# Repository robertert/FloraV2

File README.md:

# Doniczka-robot

Autonomiczna, solarna, mobilna doniczka: jezdzi po trawniku za sloncem, mierzy
warunki i sama podlewa rosline. Praca inzynierska AGH, termin styczen 2027.

Cos nie dziala przy uruchamianiu? Zacznij od `CZESTE_BLEDY.md`.

## Uklad repozytorium

Jedno repo, dwie jednostki polaczone UART-em przez maszt, wspolne sterowniki.

```
components/        sterowniki dzielone przez obie jednostki
  flora_board/     mapa pinow bryly + przeliczniki odometrii
  flora_motors/    naped na Cytron MDD10A (PWM + DIR)
  flora_encoders/  enkodery kwadraturowe na PCNT
  flora_ina226/    pomiar pradu i napiecia szyny 12V
  flora_msgs/      kontrakt wiadomosci UART (wspolny dla obu stron)
hub/               BRYLA: ESP32-S3 DevKitC-1 N16R8
                   naped, odometria, zasilanie, podlewanie, telemetria
node/              GLOWICA MASZTU: ESP32-S3 z gniazdem kamery (do kupienia)
                   kompas sloneczny, BME280, IMU, czujnik deszczu
```

Nazwy katalogow `hub` i `node` pochodza z wczesniejszej wersji projektu.
`hub` to jednostka DOLNA, `node` to GLOWICA.

Wspolne komponenty trafiaja do obu projektow przez `EXTRA_COMPONENT_DIRS`
ustawione w `CMakeLists.txt` kazdej jednostki.

## Wymagania

ESP-IDF **v6.1**, zainstalowane przez EIM w `~/.espressif/v6.1/esp-idf`.
Obie jednostki to ESP32-S3.

## Praca z projektem

`./dev.sh` sam wciaga srodowisko ESP-IDF i wykrywa port, wiec nie trzeba
niczego sourcowac:

```sh
./dev.sh hub build      # zbuduj bryle
./dev.sh hub fm         # build + flash + monitor, najczestszy cykl
./dev.sh hub monitor    # sama konsola, wyjscie Ctrl+]
./dev.sh hub menuconfig
./dev.sh ports          # co widac na USB
./dev.sh help           # pelna lista komend
```

Nieznane komendy leca wprost do `idf.py`, np. `./dev.sh hub partition-table`.

Przy dwoch podlaczonych plytkach trzeba wskazac port:
`FLORA_PORT=/dev/cu.usbmodem101 ./dev.sh hub fm`.

## Debug przez MQTT

Bryla publikuje wszystko, co do niej dociera (wlasne czujniki i wiadomosci
glowicy), pod `flora/robot1/tele/*` i `flora/robot1/head/*`, a komendy
przyjmuje z `flora/robot1/cmd/*` (opis w `hub/main/hub_remote.h`).

1. Broker na Macu (`brew install mosquitto`):
   `mosquitto -c tools/dashboard/mosquitto.conf -v`
2. Adres brokera dla robota to IP Maca w tej samej sieci:
   `FLORA_MQTT_URI_DEFAULT` w `flora_board.h` albo klucz `mqtt_uri` w NVS.
3. Panel: otworz `tools/dashboard/index.html` w przegladarce, adres
   `ws://<ip-maca>:9001`. Strzalki na klawiaturze jada, spacja to STOP.
4. Z terminala: `mosquitto_sub -t 'flora/robot1/#' -v`,
   `mosquitto_pub -t flora/robot1/cmd/pump -m on`.

Naped z panelu staje sam po 1,5 s bez odswiezenia komendy (dead-man),
wiec zerwane WiFi nie zostawi jadacego robota.

**Do jakiego brokera laczy sie robot** - po kolei, az ktorys odpowie:

1. ustawienia z NVS (zmieniane zdalnie, patrz nizej),
2. serwer wkompilowany w firmware (`FLORA_MQTT_URI_DEFAULT` w `flora_board.h`,
   TLS, login `robot1`, haslo z NVS - w kodzie go nie ma),
3. broker na Macu po nazwie mDNS (`Roberts-MacBook-Pro.local`), bez hasel.

Haslo brokera trzeba wpisac raz (`cmd/config/mqtt_pass`, z lokalnego panelu,
gdy robot jest na brokerze Maca). Przezywa zwykle flashowanie, znika dopiero
po `erase-flash`.

**Ustawienia zdalnie** (karta "Ustawienia" w panelu albo z terminala), zapis
do NVS, siec i broker dzialaja po restarcie:

```sh
mosquitto_pub -t flora/robot1/cmd/config/mqtt_uri -m mqtt://172.20.10.14:1883
mosquitto_pub -t flora/robot1/cmd/reboot -m 1
```

Klucze: `wifi_ssid`, `wifi_pass`, `mqtt_uri`, `mqtt_user`, `mqtt_pass`,
`soil_dry`, `soil_wet`; wartosc `-` kasuje ustawienie. Zly adres albo haslo
w NVS nie wymaga podlaczania kabla - robot przejdzie do kolejnych prob.

**Diagnostyka zdalna** (`hub/main/hub_diag.c`):

- `tele/log` - ostrzezenia i bledy z logu ESP (poziomy W i E). Kolejka
  trzyma je takze bez polaczenia, wiec bledy z uruchamiania i z przerwy w
  sieci wychodza po polaczeniu. Konsola USB dostaje wszystko jak dotad.
- `tele/boot` (retain) - wersja firmware, data budowania, powod ostatniego
  restartu (`panic`, `task_wdt`, `brownout`... = awaria) i licznik startow.

Wersja firmware pochodzi z tagu `hub-vX.Y.Z` (`git tag hub-v0.1.0`); bez
niego jest skrot commita. Tagi `server-v...` sa dla serwera i do firmware
nie trafiaja.

**Historia** (Telegraf + InfluxDB + Grafana w Dockerze):

```sh
cd tools/telemetry && docker compose up -d
```

Grafana pod http://localhost:3001 (admin / flora-admin), dashboard
"Flora robot". Wersja na serwer (broker z TLS i haslami, Grafana i
panel za HTTPS): `tools/server/README.md`. Hasla domyslne sa tylko do laptopa - na serwer ustaw wlasne
w `tools/telemetry/.env` (`INFLUX_PASSWORD`, `INFLUX_TOKEN`, `GRAFANA_PASSWORD`).

## Glowica w sieci

Glowica ma wlasne WiFi i polaczenie z brokerem (`node/main/head_net.c`),
niezalezne od UART-u w maszcie - da sie ja debugowac bez kabla i takze wtedy,
gdy lacze z bryla nie dziala. Ten sam login co bryla (`robot1`), ta sama baza
tematow, osobne nazwy:

| Temat | Co |
|---|---|
| `headstatus` | `online` / `offline` (retain + testament) |
| `head/log` | logi W i E, caly start, wiecej na zadanie |
| `head/boot` | wersja, powod restartu, licznik startow |
| `head/ota` | stan aktualizacji |
| `headcmd/<x>` | komendy, odpowiedz w `headack/<x>` |

Komendy: `log` (`"slow D"`), `reboot`, `ota` (`latest` albo `head-v1.2.0`),
`config/<klucz>` (`wifi_ssid`, `wifi_pass`, `mqtt_uri`, `mqtt_user`,
`mqtt_pass`; `-` kasuje, dziala po restarcie).

```sh
mosquitto_sub -t 'flora/robot1/head/log' -v
mosquitto_pub -t flora/robot1/headcmd/log -m 'slow D'
```

W panelu: kropka "glowica" u gory, karty "Start glowicy" i "Glowica: serwis
i OTA", a logi obu jednostek sa na jednej liscie z filtrem.

**Pierwsze uruchomienie.** Haslo brokera glowica trzyma we wlasnym NVS, wiec
trzeba je wpisac raz: bez hasla glowica laczy sie z brokerem na Macu
(krok 1 w "Debug przez MQTT"), tam `headcmd/config/mqtt_pass`, potem
`headcmd/reboot`. Wspolne klocki z bryla: `components/flora_net`,
`flora_diag`, `flora_ota`. Wylacznik: `FLORA_HEAD_NET_DEFAULT` w
`flora_head_board.h`.

## Aktualizacja przez siec (OTA)

Bryla ma dwa sloty aplikacji (`hub/partitions.csv`). Nowa wersja laduje do
wolnego, a stara zostaje jako zapas:

1. `git tag hub-v1.2.0 && git push origin hub-v1.2.0` - CI buduje firmware i
   wrzuca go na serwer (`tools/server/README.md`, sekcja OTA).
2. Panel, karta "Aktualizacja (OTA)": "aktualizuj do najnowszej" albo
   konkretna wersja. Naped i pompka musza stac.
3. Robot pobiera po HTTPS z serwera, sprawdza SHA-256 z manifestem i sie
   restartuje. Postep i wynik na `tele/ota`.
4. Nowa wersja startuje "na probe": potwierdza sie sama po minucie stabilnego
   polaczenia z brokerem. Bez polaczenia przez 5 min albo po awarii przed
   potwierdzeniem bootloader wraca do poprzedniej, a `tele/boot` pokazuje ja
   w `rolled_back`.

Glowica dziala tak samo, z wlasnymi tagami: `git tag head-v0.1.0`, karta
"Glowica: serwis i OTA" w panelu, postep na `head/ota`, sloty w
`node/partitions.csv`. Nic jej nie blokuje (nie ma napedu ani pompki).

Tablicy partycji nie da sie zmienic przez OTA. Zmiana `hub/partitions.csv`
albo `node/partitions.csv` oznacza flashowanie kablem. NVS lezy w tym samym miejscu co w dawnym ukladzie,
wiec przejscie na OTA nie kasuje hasla brokera ani kalibracji.

## Podglad kamery i zbieranie danych

Glowica w trybie podgladu stawia serwer HTTP i nadaje strumien MJPEG. Adres
pojawia sie w logu po starcie (`./dev.sh node monitor`):

```
http://<ip-glowicy>/      zywy obraz w przegladarce
http://<ip-glowicy>/jpg   jedna klatka, np. curl -o kadr.jpg http://<ip>/jpg
```

**Domyslnie obraz NIE jest dostepny przez siec.** Glowica wstaje bez WiFi i
bez serwera HTTP: obrazu nikt nie oglada, a jedynym odbiorca jest detektor
przeszkod. Radio na solarnej glowicy to najwiekszy pojedynczy pobor, a serwer
HTTP ma wyzszy priorytet niz wizja i walczy z nia o kamere (zmierzone: przy
otwartej stronie czas na klatke skakal z 233 ms na 1728 ms). Linker wyrzuca
wtedy caly stos sieciowy, wiec obraz aplikacji schodzi z 1034 kB do 398 kB.

Podglad wlacza sie przez `FLORA_HEAD_CAM_NET_DEFAULT 1` w `flora_head_board.h`
i przeflashowanie - do wycelowania kamery, zebrania klatek albo ustawienia jej
wysokosci. Wtedy dopiero dziala ponizsze:

Kamera przyjmuje JEDEN format na uruchomienie, wiec glowica ma dwa tryby i
przelacza je przez `http://<ip>/mode?v=jpeg` albo `?v=raw` (zapis do NVS i
restart, okolo dwoch sekund):

| tryb | do czego | endpointy |
|---|---|---|
| `jpeg` | celowanie kamery, ocena ostrosci | `/stream`, `/jpg` |
| `raw` | zbieranie zbioru, 320x240 RGB565 | `/raw` |

Zbior zbieramy w trybie **raw**, nie JPEG: kompresja podprobkowuje chrominancje
4:2:0 i doklada artefakty blokow, czyli psuje dokladnie ten sygnal, na ktorym
stoi wykrywanie przeszkod. Prototyp na Macu musi widziec te same bajty, ktore
zobaczy pozniej algorytm na ESP.

## Narzedzia wizyjne (`tools/vision/`)

Zadnych zaleznosci z pip - sama biblioteka standardowa Pythona i `mosquitto_sub`
z brew.

```sh
# zbieranie: klatki + migawka telemetrii z MQTT do kazdej
collect.py --host 192.168.1.42 --surface kostka --light slonce --raw
collect.py --host 192.168.1.42 --surface beton --light cien --raw --no-mqtt

# prototyp wykrywania: nakladka PNG + linia JSON na klatke
ground.py data/20261101-kostka-slonce/*.rgb565

# syntetyczne klatki o znanej odpowiedzi, do testow bez kamery
synth.py /tmp/test.rgb565 --joints --shadow 90 --obstacle -50,80,24
```

`ground.py` pracuje na siatce POLARNEJ wokol srodka kadru, bo kamera patrzy
prosto w dol: PIERSCIEN to odleglosc (0 najblizej), WYCINEK to kierunek
(16 sztuk, od lewej do prawej, jak `sectors[]` w kontrakcie). W wyniku `12`
znaczy czysto do konca zasiegu, a `-1` nieznane. Przelacznik `--grid` rysuje
granice i numery wycinkow wprost na kadrze - bez tego trzeba liczyc wycinki
palcem po ekranie. Sesje lezą w `tools/vision/data/` i NIE sa w repo.

## Testy hostowe

Filtry, kalibracje, regulator i logika funkcji autonomicznych to czysty C -
sprawdzane na komputerze, takze
w CI przy kazdym pushu (`.github/workflows/tests.yml`), z AddressSanitizer
i UBSan:

```sh
sh tools/host_tests.sh
```

## Nagrywanie i odtwarzanie przejazdow (`tools/rec/`)

Bryla na `cmd/rec on` wysyla na `rec/data` surowe wejscia nawigacji z kazdego
taktu (enkodery, kurs i zyro z glowicy, slonce, znaczniki). Na komputerze ten
sam kod filtra (`components/flora_nav`, `flora_navcore`) liczy je od nowa -
bez zmian wychodzi to samo co na robocie, a ze zmienionym strojeniem albo
kalibracja widac, co by bylo, na tym samym przejezdzie.

```sh
tools/rec/record.py --start -o kwadrat.log      # Ctrl+C konczy
cd components/flora_nav/host
cc -O2 -Wall -I../include -o replay replay.c ../flora_navcore.c \
   ../flora_ekf.c ../flora_sun.c ../flora_sungate.c -lm
./replay --end "0 0" kwadrat.log                 # blad zamkniecia kazdego wariantu
./replay --head-floor 6 --deadband 3 kwadrat.log # inne strojenie
./replay --csv traj.csv kwadrat.log && ../../../tools/rec/plot.py traj.csv --tags kwadrat.log
sh replay_test.sh                                # test toru na syntetycznym nagraniu
```

Format linii: `components/flora_nav/include/flora_navlog.h`. Nagrania nie sa w repo.

## Wykrywanie przeszkod

Modul tagcam (kamera 160 stopni w dol) liczy 16 odleglosci i wysyla je
przez glowice w dol jako `FLORA_MSG_OBSTACLES` (`components/flora_ground`
plus `tagcam/main/main.c`, 4 Hz). Bryla publikuje je na `head/obstacles`.
Do 21.11.2026 robila to glowica, a tagcam szukal znacznikow - role kamer
zostaly zamienione.

Nie uczymy sie, jak wyglada przeszkoda - w kazdej klatce od nowa uczymy sie,
jak wyglada PODLOZE tuz przy kamerze, i szukamy, gdzie przestaje tak wygladac.
Dlatego to samo dziala na kostce, betonie i trawie bez zadnego uczenia.
Porownanie idzie po BARWIE, nie po jasnosci, zeby cien nie byl przeszkoda.

Zanim sektory zaczna niesc centymetry, trzeba zmierzyc wysokosc obiektywu nad
ziemia i wpisac ja w `FLORA_HEAD_CAM_HEIGHT_MM`. Bez tego ida jako "nie wiem".

Rdzen algorytmu nie zalezy od ESP-IDF i kompiluje sie zwyklym gcc, co sluzy
do sprawdzania, czy wersja na robocie liczy to samo co prototyp:

```sh
cd components/flora_ground/host
cc -O2 -I../include -o runner runner.c ../flora_ground.c -lm
./runner --r-in 2 ../../../tools/vision/data/<sesja>/*.rgb565
```

Po KAZDEJ zmianie algorytmu porownaj wynik z `tools/vision/ground.py` na tych
samych klatkach. Uwaga: harness NIE wykryje bledow pamieci, bo na komputerze
stos ma megabajty - tak przeszlo przepelnienie stosu, ktore na ESP wywalalo
zadanie po dwoch sekundach.

## Funkcje autonomiczne (domyslnie WYLACZONE)

Kod petli wysokiego poziomu jest w firmware bryly, ale kazda funkcja ma
wlasny przelacznik w NVS i po wgraniu wszystkie sa na 0 - robot zachowuje
sie jak bez nich. Wlaczanie pojedynczo, bez flashowania:

```sh
mosquitto_pub -t flora/robot1/cmd/config/guard_en -m 1
mosquitto_sub -t 'flora/robot1/config_auto' -v    # stan przelacznikow
```

| Przelacznik | Co wlacza | Logika (czysty C, test hostowy) | Na robocie | Stan |
|---|---|---|---|---|
| `guard_en` | straznik napedu: weto przeszkod (kamera, sonary), przechyl, napiecie, stare dane | `flora_guard` | `hub_safety` | `tele/safety` |
| `pilot_en` | jazda do punktu: `cmd/goto "x y [th]"`, `cmd/turn "th"` | `flora_pilot` | `hub_pilot` | `tele/pilot` |
| `water_en` | podlewanie z histereza wilgotnosci | `flora_water` | `hub_water` | `tele/water` |
| `mission_en` | szukanie slonca: ucieczka z cienia w granicach `cmd/area` | `flora_seek`, `flora_mission` | `hub_mission` | `tele/mission` |
| `sleep_en` | gleboki sen i wylaczanie masztu wg napiecia i pory | `flora_energy` | `hub_power` | `tele/energy` |
| `mdd_key_en` | klucz 12 V sterownika MDD10A na GPIO42 | - | `hub_power` | - |

Progi i pelna lista kluczy: `hub/main/hub_autocfg.h`. Opis kazdego modulu
w jego naglowku. Kolejnosc wlaczania i testy: `TESTY_RECZNE.md`, punkt 8.

Wszystkie zadania mocy na silniki ida przez `hub_drive` (`hub_drive_set_power`,
`hub_drive_set_speed`), ktory pyta straznika o zgode - takze reczna jazda
z panelu i kalibracje. Przy `guard_en = 0` straznik zawsze sie zgadza.

Spiacego robota wylacza sie wiadomoscia z retain, ktora odbierze po
najblizszym wybudzeniu:
`mosquitto_pub -r -t flora/robot1/cmd/config/sleep_en -m 0`.

## Stan

Bryla ma naped z petla predkosci, odometrie i EKF pozycji, pomiar pradu,
czujniki (gleba, poziom wody, dalmierze, DS18B20), telemetrie MQTT, OTA
i zdalne sterowanie z panelu. Glowica ma fuzje kursu, kompas sloneczny,
BME280, oba lacza UART i kamere pozioma 68 stopni, ktora wykrywa znaczniki
AprilTag (`node/main/head_tags.c`). Osobna plytka w maszcie (tagcam) ma
kamere OV5640 160 stopni patrzaca w dol i wykrywa przeszkody: 16 sektorow
idzie przez glowice do bryly (centymetry dopiero po wpisaniu wysokosci
obiektywu).

Petle wysokiego poziomu (straznik, jazda do punktu, podlewanie, szukanie
slonca, sen) sa napisane i przetestowane na komputerze, ale NIE sprawdzone
na sprzecie i domyslnie wylaczone - patrz wyzej.

**Uwaga przy uruchamianiu testu napedu: kola musza byc w powietrzu.**

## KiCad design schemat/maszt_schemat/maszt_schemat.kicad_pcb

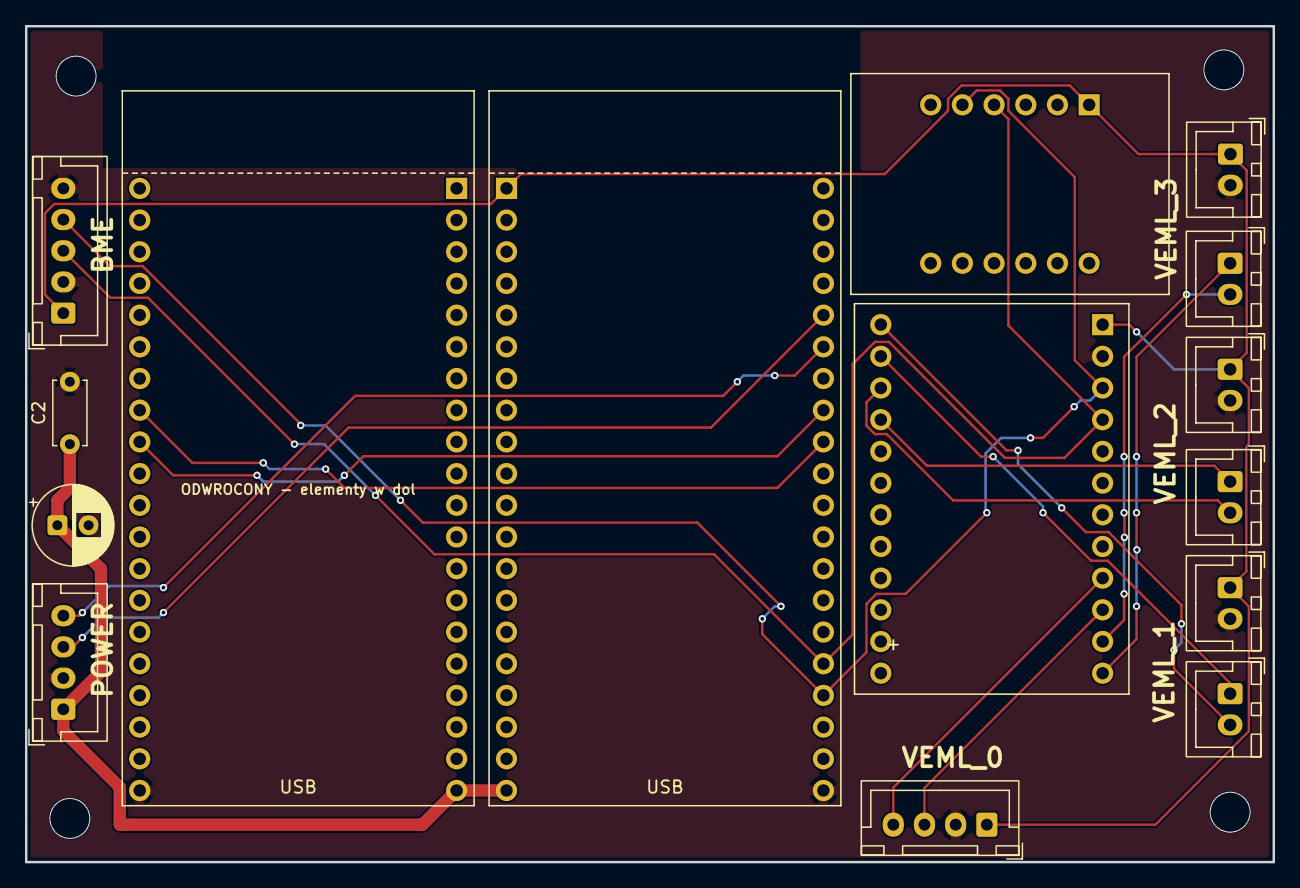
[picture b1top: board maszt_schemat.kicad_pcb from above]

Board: 2 copper layers, 100.0 x 67.0 mm, 15 parts (0 on the bottom side), 17 nets.

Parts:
C1: C_Polarized; CP_Radial_D6.3mm_P2.50mm
C2: C; C_Disc_D5.0mm_W2.5mm_P5.00mm
J1, J2: Conn_01x04; JST_XH_B4B-XH-A_1x04_P2.50mm_Vertical
J4, J6, J7, J8, J9, J10: Conn_01x02; JST_XH_B2B-XH-A_1x02_P2.50mm_Vertical
J5: Conn_01x05; JST_XH_B5B-XH-A_1x05_P2.50mm_Vertical
U2: ESP32-S3-CAM N16R8; ESP32-S3-CAM
U3: ICM-20948; ICM-20948_Adafruit
U4: TCA9548A; TCA9548A_Module
U9: ESP32-S3-CAM N16R8; ESP32-S3-CAM_Mirrored

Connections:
+3.3V: J2.1, J5.1, J7.1, J9.1, J10.1, U2.1 (3V3), U3.1 (VIN), U4.1 (VIN)
+5V: C1.1, C2.1, J1.1, U2.20 (5V), U9.20 (5V)
GND: C1.2, C2.2, J1.2, J2.2, J5.2, J5.5, J7.2, J9.2, J10.2, U2.40 (GND), U3.3 (GND), U4.2 (GND), U9.40 (GND)
unnamed: J1.3, U2.25 (GPIO42)
unnamed: J1.4, U2.26 (GPIO41)
unnamed: J2.3, U4.10 (SC0)
unnamed: J2.4, U4.9 (SD0)
unnamed: J4.1, U4.12 (SC1)
unnamed: J4.2, U4.11 (SD1)
unnamed: J5.3, U2.36 (GPIO47), U3.4 (SCL), U4.4 (SCL)
unnamed: J5.4, U2.37 (GPIO21), U3.5 (SDA), U4.3 (SDA)
unnamed: J6.1, U4.14 (SC2)
unnamed: J6.2, U4.13 (SD2)
unnamed: J8.1, U4.16 (SC3)
unnamed: J8.2, U4.15 (SD3)
unnamed: U2.29 (GPIO38), U9.28 (GPIO39)
unnamed: U2.28 (GPIO39), U9.29 (GPIO38)

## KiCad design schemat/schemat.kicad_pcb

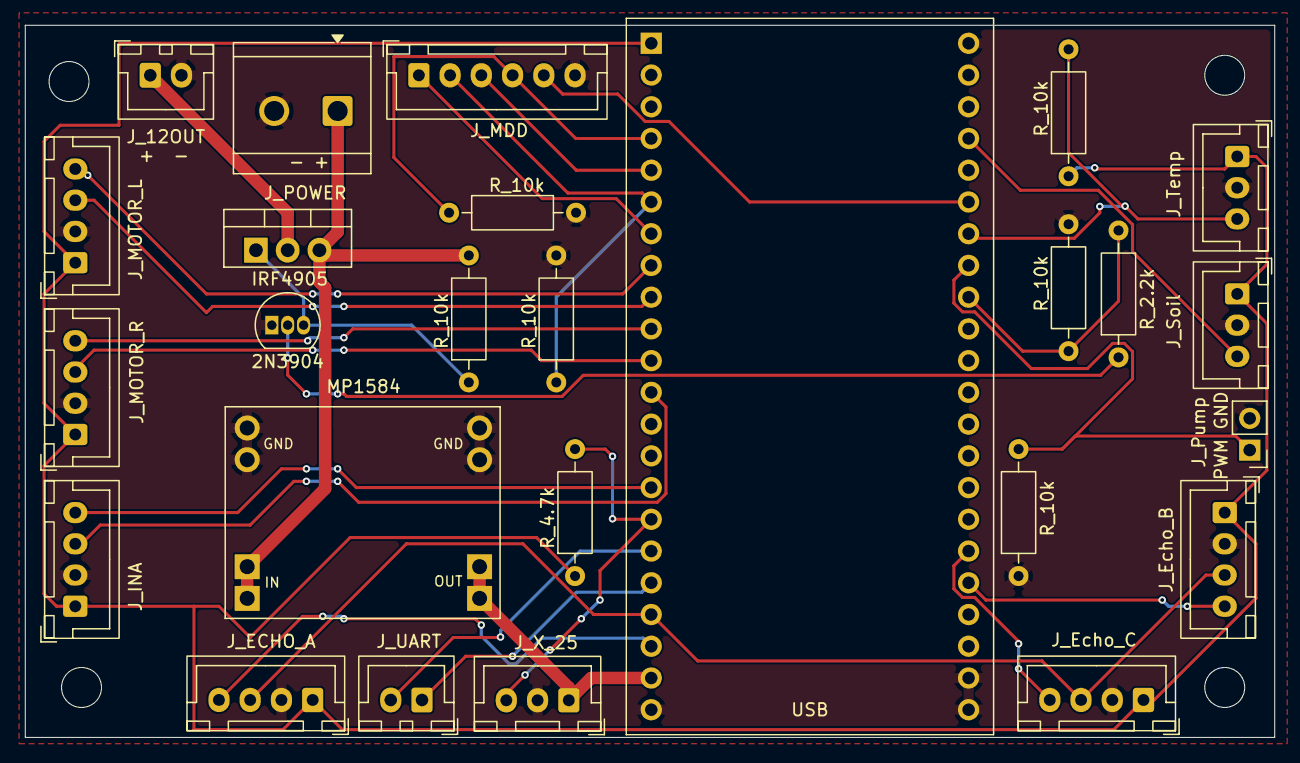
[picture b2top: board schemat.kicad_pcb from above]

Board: 2 copper layers, 100.0 x 57.0 mm, 26 parts (0 on the bottom side), 29 nets.

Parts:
J2: INA JSX; JST_XH_B4B-XH-A_1x04_P2.50mm_Vertical
J3: JSX_Motor_L; JST_XH_B4B-XH-A_1x04_P2.50mm_Vertical
J4: JSX_MDD; JST_XH_B6B-XH-A_1x06_P2.50mm_Vertical
J5: JSX_Motor_R; JST_XH_B4B-XH-A_1x04_P2.50mm_Vertical
J6: JSX_Temp; JST_XH_B3B-XH-A_1x03_P2.50mm_Vertical
J7: 12VOUT; JST_XH_B2B-XH-A_1x02_P2.50mm_Vertical
J8: JSX_ECHO_A; JST_XH_B4B-XH-A_1x04_P2.50mm_Vertical
J9: JSX_ECHO_B; JST_XH_B4B-XH-A_1x04_P2.50mm_Vertical
J10: JSX_ECHO_C; JST_XH_B4B-XH-A_1x04_P2.50mm_Vertical
J11: JSX-X25; JST_XH_B3B-XH-A_1x03_P2.50mm_Vertical
J12: JSX_Soil; JST_XH_B3B-XH-A_1x03_P2.50mm_Vertical
J13: Conn_01x02; TerminalBlock_CUI_TB007-508-02_1x02_P5.08mm_Horizontal
J14: JSX_UART; JST_XH_B2B-XH-A_1x02_P2.50mm_Vertical
J15: Pump-mosfet-Pins; PinHeader_1x02_P2.54mm_Vertical
Q1: IRF4905; TO-220-3_Vertical
Q2: 2N3904; TO-92_Inline
R1, R2, R4, R6, R7, R8: R 10k; R_Axial_DIN0207_L6.3mm_D2.5mm_P10.16mm_Horizontal
R3: R 2,2k; R_Axial_DIN0207_L6.3mm_D2.5mm_P10.16mm_Horizontal
R5: R 4,7k; R_Axial_DIN0207_L6.3mm_D2.5mm_P10.16mm_Horizontal
U2: ESP32-S3-DevKitC-1
U3: MP1584; MP1584_Module

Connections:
+3.3V: J2.1, J3.1, J5.1, J6.1, J8.1, J9.1, J10.1, J12.1, R4.1, R5.1, U2.1 (3V3)
+5V: J11.1, U2.21 (5V), U3.3 (OUT+)
+12V: J13.1, Q1.3 (S), R2.2, U3.1 (IN+)
GND: J2.2, J3.2, J4.6, J5.2, J6.2, J7.2, J8.2, J9.2, J10.2, J11.2, J12.2, J13.2, J15.2, Q2.1 (E), R1.2, R6.2, R7.2, R8.1, U2.22 (GND), U2.23 (GND), U2.43 (GND), U2.44 (GND), U3.2 (IN-), U3.4 (OUT-)
unnamed: J2.3, U2.12 (GPIO8)
unnamed: J2.4, U2.15 (GPIO9)
unnamed: J3.3, U2.9 (GPIO16)
unnamed: J3.4, U2.8 (GPIO15)
unnamed: J4.1, U2.7 (GPIO7)
unnamed: J4.2, R6.1, U2.6 (GPIO6)
unnamed: J4.3, U2.5 (GPIO5)
unnamed: J4.4, R7.1, U2.4 (GPIO4)
unnamed: J4.5, U2.28 (GPIO42)
unnamed: J5.3, U2.11 (GPIO18)
unnamed: J5.4, U2.10 (GPIO17)
unnamed: J6.3, R4.2, U2.29 (GPIO41)
unnamed: J7.1, Q1.2 (D)
unnamed: J8.4, U2.20 (GPIO14)
unnamed: J9.4, U2.40 (GPIO21)
unnamed: J8.3, J9.3, J10.3, U2.19 (GPIO13)
unnamed: J10.4, U2.39 (GPIO47)
unnamed: J11.3, R5.2, U2.16 (GPIO10)
unnamed: J12.3, U2.26 (GPIO1)
unnamed: J14.1, U2.18 (GPIO12)
unnamed: J14.2, U2.17 (GPIO11)
unnamed: J15.1, R8.2, U2.30 (GPIO40)
unnamed: Q1.1 (G), Q2.3 (C), R2.1
unnamed: Q2.2 (B), R3.1
unnamed: R1.1, R3.2, U2.31 (GPIO39)
